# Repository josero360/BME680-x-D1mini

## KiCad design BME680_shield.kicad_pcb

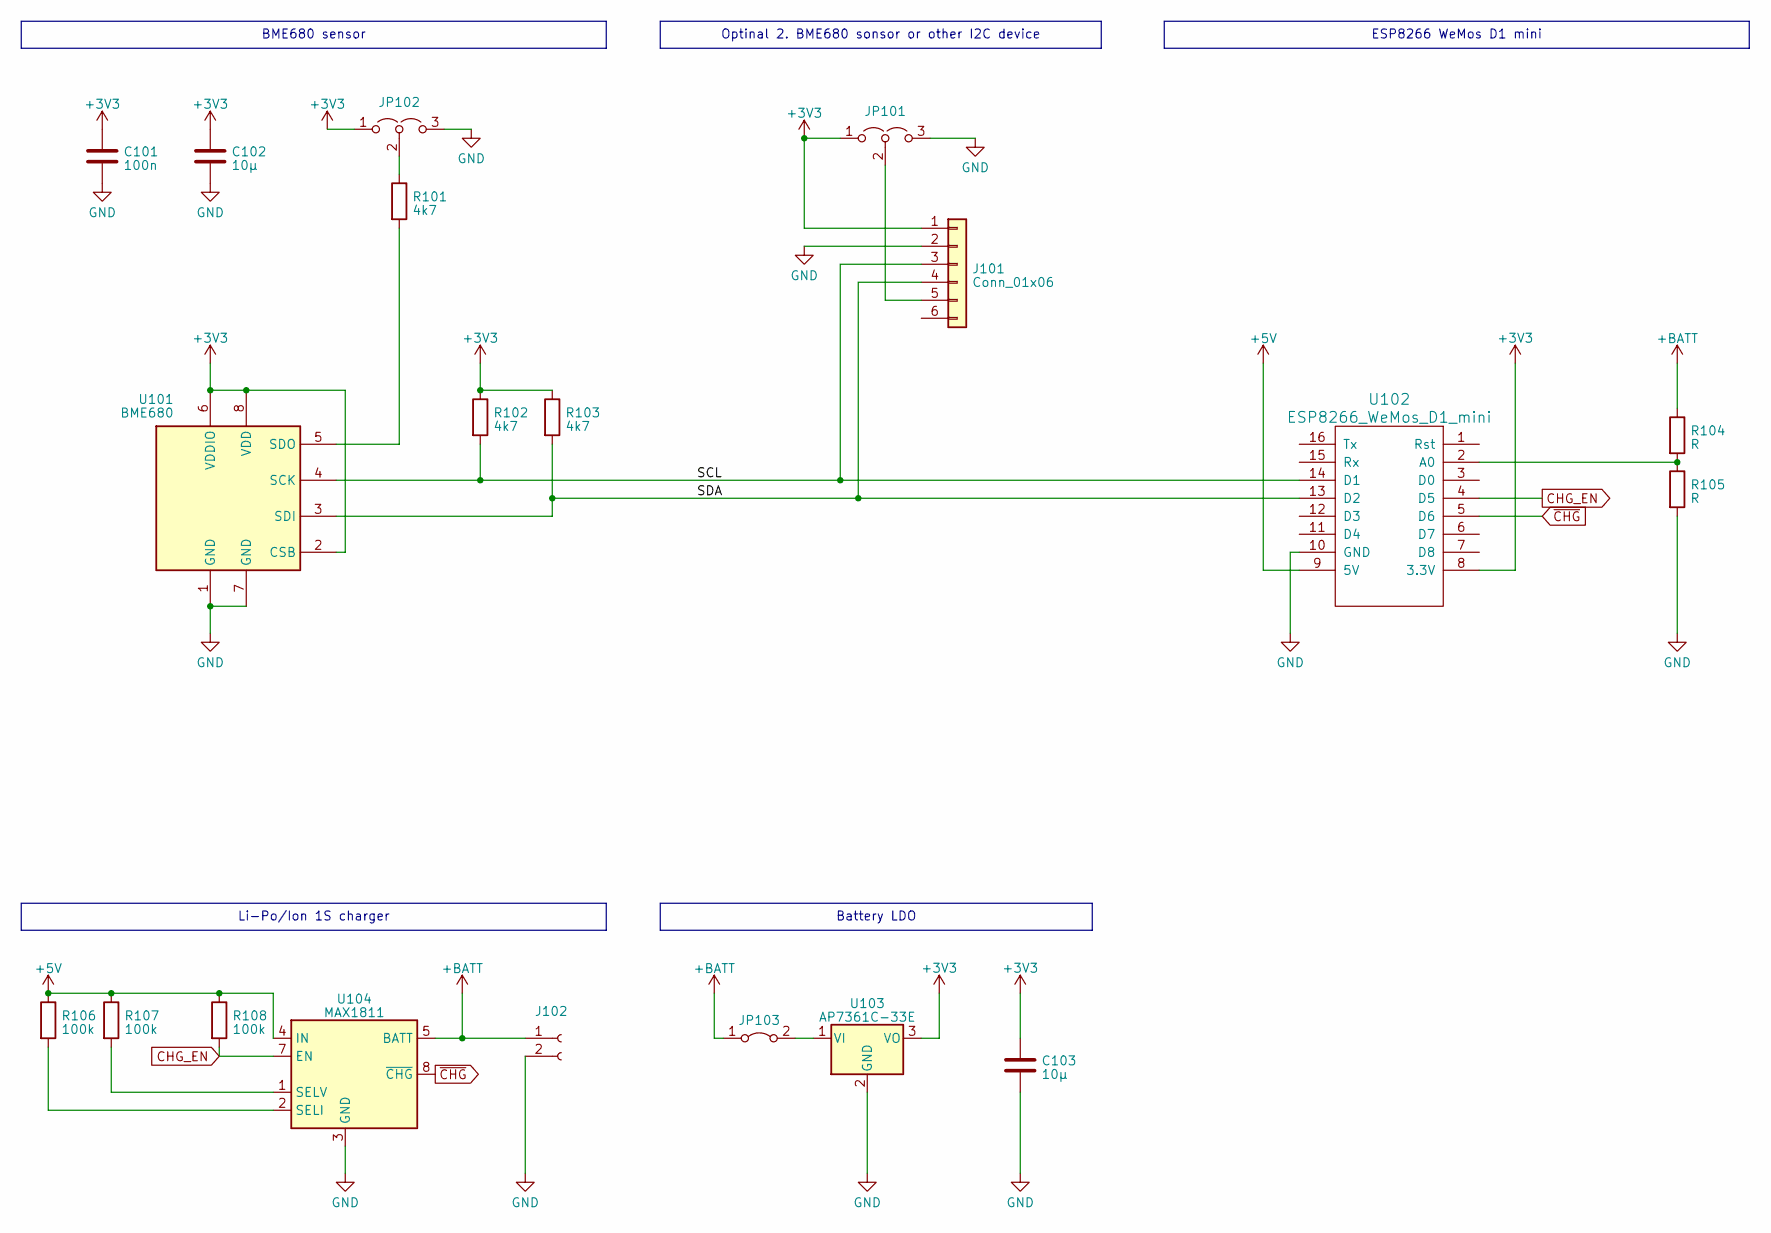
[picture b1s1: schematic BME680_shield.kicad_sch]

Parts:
C101: 100n; C_0805_2012Metric_Pad1.18x1.45mm_HandSolder
C102, C103: 10µ; C_0805_2012Metric_Pad1.18x1.45mm_HandSolder
J101: Conn_01x06; PinHeader_1x06_P2.54mm_Vertical
J102: Conn_01x02_Socket; PinHeader_1x02_P2.54mm_Vertical
JP101, JP102: Jumper_3_Open; SolderJumper-3_P1.3mm_Open_Pad1.0x1.5mm
JP103: Jumper_2_Bridged; PinHeader_1x02_P2.54mm_Vertical
R101, R102, R103: 4k7; R_0805_2012Metric_Pad1.20x1.40mm_HandSolder
R104, R105: R; R_0805_2012Metric_Pad1.20x1.40mm_HandSolder
R106, R107, R108: 100k; R_0805_2012Metric_Pad1.20x1.40mm_HandSolder
U101: BME680; Bosch_LGA-8_3x3mm_P0.8mm_ClockwisePinNumbering
U102: ESP8266_WeMos_D1_mini; wemos-d1-mini-connectors-only
U103: AP7361C-33E; SOT-89-5_Handsoldering
U104: MAX1811; SOIC-8_3.9x4.9mm_P1.27mm

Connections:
+3V3: C101.1, C102.1, C103.1, J101.1, JP101.1 (A), JP102.1 (A), R102.1, R103.1, U101.2 (CSB), U101.6 (VDDIO), U101.8 (VDD), U102.8 (3.3V), U103.3 (VO)
+5V: R106.1, R107.1, R108.1, U102.9 (5V), U104.4 (IN)
+BATT: J102.1, JP103.1 (A), R104.1, U104.5 (BATT)
CHG_EN: R108.2, U102.4 (D5), U104.7 (EN)
GND: C101.2, C102.2, C103.2, J101.2, J102.2, JP101.3 (B), JP102.3 (B), R105.2, U101.1 (GND), U101.7 (GND), U102.10 (GND), U103.2 (GND), U104.3 (GND), U104.6 (GND)
unnamed: J101.3, R102.2, U101.4 (SCK), U102.14 (D1)
unnamed: J101.4, R103.2, U101.3 (SDI), U102.13 (D2)
unnamed: J101.5, JP101.2 (C)
unnamed: JP102.2 (C), R101.1
unnamed: JP103.2 (B), U103.1 (VI)
unnamed: R101.2, U101.5 (SDO)
unnamed: R104.2, R105.1, U102.2 (A0)
unnamed: R106.2, U104.2 (SELI)
unnamed: R107.2, U104.1 (SELV)
~CHG: U102.5 (D6), U104.8 (~CHG)

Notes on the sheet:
Li-Po/Ion 1S charger
Optinal 2. BME680 sonsor or other I2C device
Battery LDO
BME680 sensor
ESP8266 WeMos D1 mini

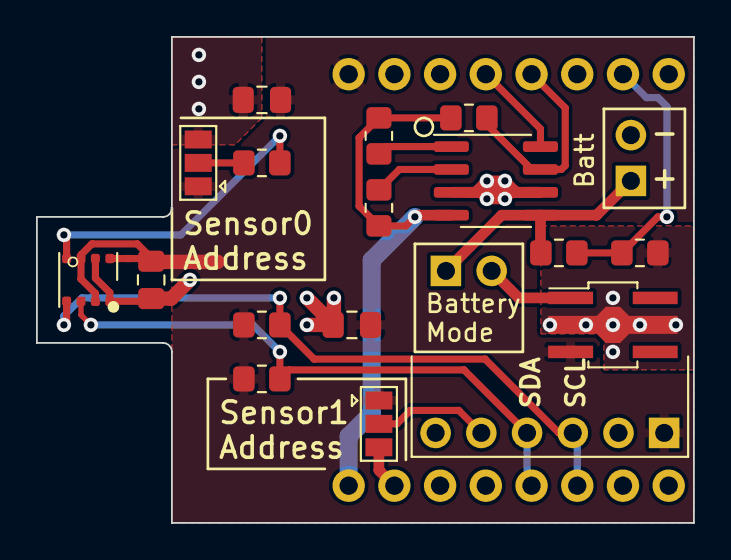
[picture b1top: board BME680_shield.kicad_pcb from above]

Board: 2 copper layers, 36.5 x 27.0 mm, 20 parts (0 on the bottom side), 15 nets.

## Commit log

2023-04-14 Inital Commit
2023-04-17 push after order
2023-05-09 Leiterpaltte aufgebaut
